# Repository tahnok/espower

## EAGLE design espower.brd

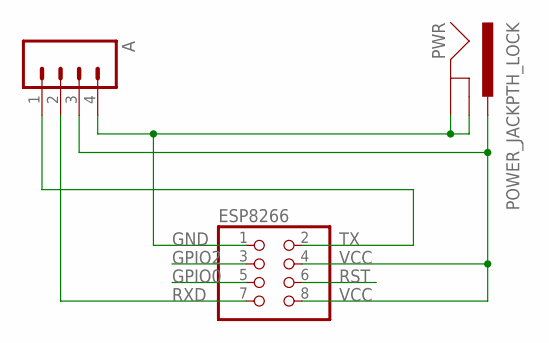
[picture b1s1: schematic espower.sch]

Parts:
A: M04PTH; 1X04
ESP8266: PINHD-2X4; 2X04
PWR: POWER_JACKPTH_LOCK; POWER_JACK_PTH_LOCK

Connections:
GND: A.4, ESP8266.1, PWR.GND, PWR.GNDBREAK
GPIO0: ESP8266.5
GPIO2: ESP8266.3
RST: ESP8266.6
RXD: A.2, ESP8266.7
TX: A.1, ESP8266.2
VCC: A.3, ESP8266.4, ESP8266.8, PWR.PWR

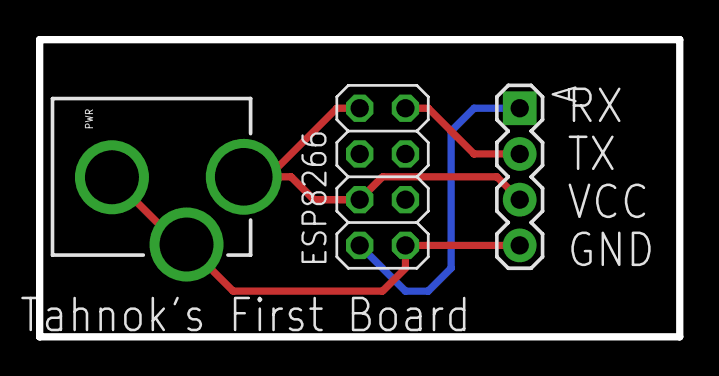
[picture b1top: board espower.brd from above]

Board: 2 copper layers, 35.6 x 16.5 mm, 3 parts (0 on the bottom side), 4 nets.

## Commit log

2015-06-07 first board!

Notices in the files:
parts and their libraries:
SparkFun-Connectors: Licensing: Creative Commons ShareAlike 4.0 International - https://creativecommons.org/licenses/by-sa/4.0
